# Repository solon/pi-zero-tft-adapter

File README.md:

# pi-zero-tft-adapter

Eagle designs for a PCB to connect a Raspberry Pi Zero to an [Adafruit 2.2" TFT LCD](https://www.adafruit.com/products/1480).

| LCD Pin | RPi Pin | RPi Pin # |
|---------|---------|-----------|
| BL_LED  | GPIO_18 | 12        |
| SCK     | SCLK    | 23        |
| MISO    | MISO	  | 21        |
| MOSI	  | MOSI	  | 19        |
| CS	    | CE0	    | 24        |
| RST	    | GPIO_25	| 22        |
| D/C	    | GPIO_24	| 18        |
| Vin	    | 3.3V	  | 17        |
| GND	    | GND	    | 20        |

Pinout taken from http://aaron-brown.net/blog/?p=99

## Order this board

You can order this board direct from OSH Park.

<a href="https://oshpark.com/shared_projects/PlSWHszO"></img></a>

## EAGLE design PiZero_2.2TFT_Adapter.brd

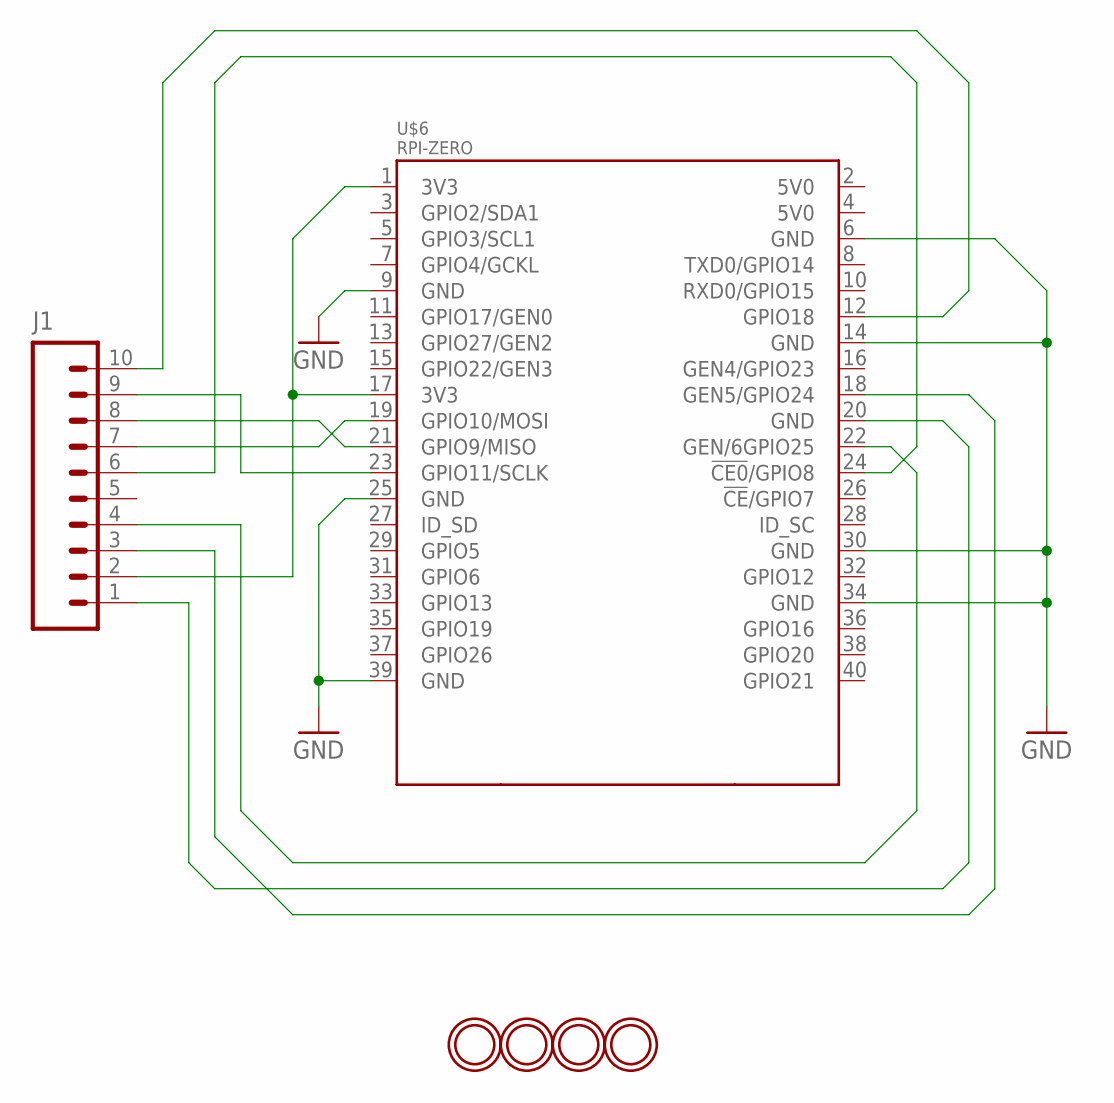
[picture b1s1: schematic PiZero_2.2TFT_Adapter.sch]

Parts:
J1: M10NO_SILK_PTH_FEMALE; 1X10_NO_SILK
U$2, U$3, U$4, U$5: MOUNTINGHOLE2.5; MOUNTINGHOLE_2.5_PLATED
U$6: RPI-ZERO; RASPBERRYPI_BASTELSTUBE_V13_RASPI_BOARD_B+_FULL

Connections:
3V3: J1.2, U$6.1 (3V3), U$6.17 (3V3)
GND: J1.1, U$6.6 (GND), U$6.9 (GND), U$6.14 (GND), U$6.20 (GND), U$6.25 (GND), U$6.30 (GND), U$6.34 (GND), U$6.39 (GND)
unnamed: J1.10, U$6.12 (GPIO18)
unnamed: J1.9, U$6.23 (GPIO11/SCLK)
unnamed: J1.8, U$6.21 (GPIO9/MISO)
unnamed: J1.7, U$6.19 (GPIO10/MOSI)
unnamed: J1.6, U$6.24 (!CE0!/GPIO8)
unnamed: J1.3, U$6.18 (GEN5/GPIO24)
unnamed: J1.4, U$6.22 (GEN/6GPIO25)

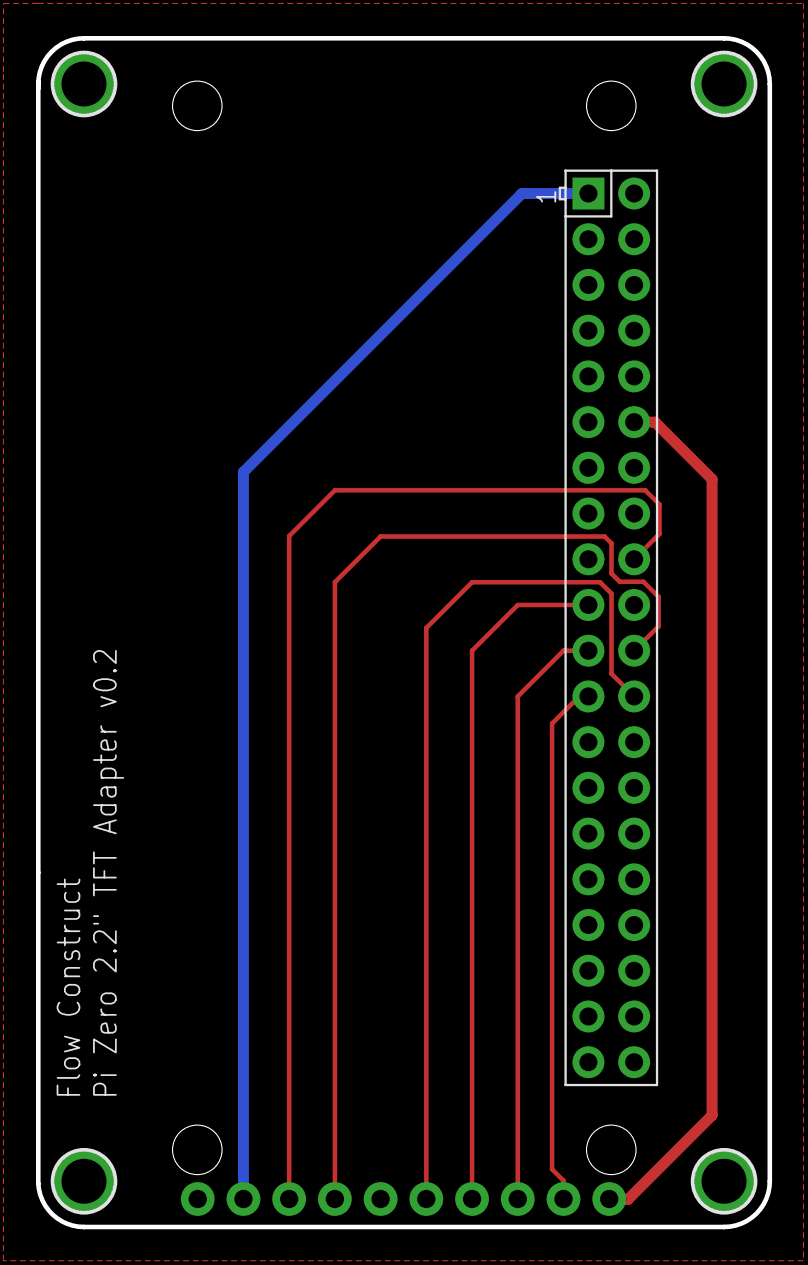
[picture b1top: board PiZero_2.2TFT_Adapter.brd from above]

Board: 2 copper layers, 40.6 x 66.0 mm, 6 parts (0 on the bottom side), 9 nets.

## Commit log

2016-07-27 Add SketchUp files
2016-08-08 Add image

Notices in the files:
parts and their libraries:
SparkFun-Connectors: Licensing: Creative Commons ShareAlike 4.0 International - https://creativecommons.org/licenses/by-sa/4.0
